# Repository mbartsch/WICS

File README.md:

WICS
====

Watering and Irrigation Control System

This is a project to integrate various devices to create a 
Control System for an irrigation system

Low Level Control:

 * USB Nano V3.0 ATmega328 16M 5V Micro-controller CH340G board For Arduino
 * Ultrasonic Sensor Module HC-SR04 Distance Measuring Sensor for arduino SR04
 * 4 Channel Relay Module With optocoupler For PIC AVR DSP ARM Arduino 8051
 * IIC I2C Logic Level Converter Bi-Directional Module 5V to 3.3V For Arduino
 * Soil Hygrometer Detection Module Soil Moisture Sensor For arduino Smart car
 * Raindrops Detection sensor modue rain module weather module Humidity For Arduino

High Level Control:
 * Raspberry Pi Model B

For the high level control, all is written in Arduino Sketch, High Level will be python/php maybe. Communication between RPi and Arduino will be over I2C (serial could be a lot easy, but I want to learn a little with this project)

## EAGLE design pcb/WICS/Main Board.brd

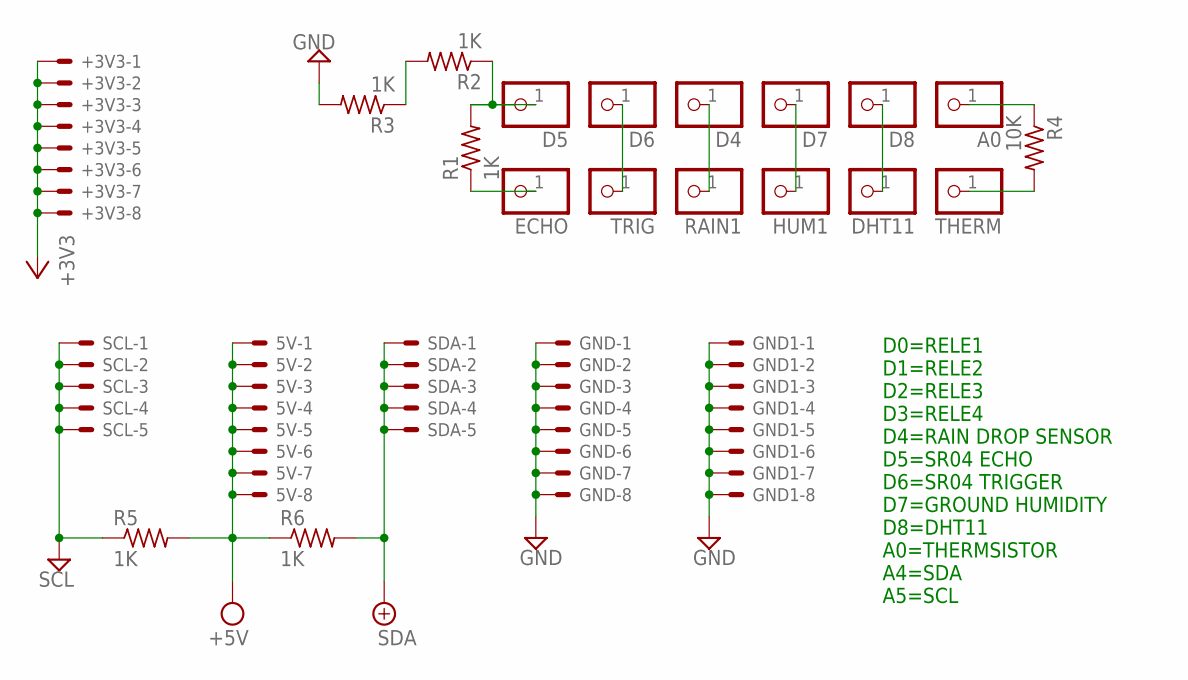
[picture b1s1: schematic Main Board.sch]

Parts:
5V: 22-23-2081
+3V3: 22-23-2081
A0: PINHD-1X1; 1X01
D4, D5, D6, D7, D8: PINHD-1X1; 1X01
DHT11: PINHD-1X1; 1X01
ECHO: PINHD-1X1; 1X01
GND, GND1: 22-23-2081
HUM1: PINHD-1X1; 1X01
R1, R2, R3, R5, R6: 1K; 0204/7
R4: 10K; 0204/7
RAIN1: PINHD-1X1; 1X01
SCL: 22-23-2051
SDA: 22-23-2051
THERM: PINHD-1X1; 1X01
TRIG: PINHD-1X1; 1X01

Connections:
+3V3: +3V3.1, +3V3.2, +3V3.3, +3V3.4, +3V3.5, +3V3.6, +3V3.7, +3V3.8
+5V: 5V.1, 5V.2, 5V.3, 5V.4, 5V.5, 5V.6, 5V.7, 5V.8, R5.2, R6.1
ECHO: ECHO.1, R1.1
GND: GND.1, GND.2, GND.3, GND.4, GND.5, GND.6, GND.7, GND.8, GND1.1, GND1.2, GND1.3, GND1.4, GND1.5, GND1.6, GND1.7, GND1.8, R3.2
GND1: R2.2, R3.1
GND3: R5.1, SCL.1, SCL.2, SCL.3, SCL.4, SCL.5
GPIO24: D5.1, R1.2, R2.1
unnamed: D6.1, TRIG.1
unnamed: A0.1, R4.1
unnamed: R4.2, THERM.1
unnamed: D4.1, RAIN1.1
unnamed: D7.1, HUM1.1
unnamed: D8.1, DHT11.1
SDA: R6.2, SDA.1, SDA.2, SDA.3, SDA.4, SDA.5

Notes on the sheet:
D0=RELE1 D1=RELE2 D2=RELE3 D3=RELE4 D4=RAIN DROP SENSOR D5=SR04 ECHO D6=SR04 TRIGGER D7=GROUND HUMIDITY D8=DHT11 A0=THERMSISTOR A4=SDA A5=SCL

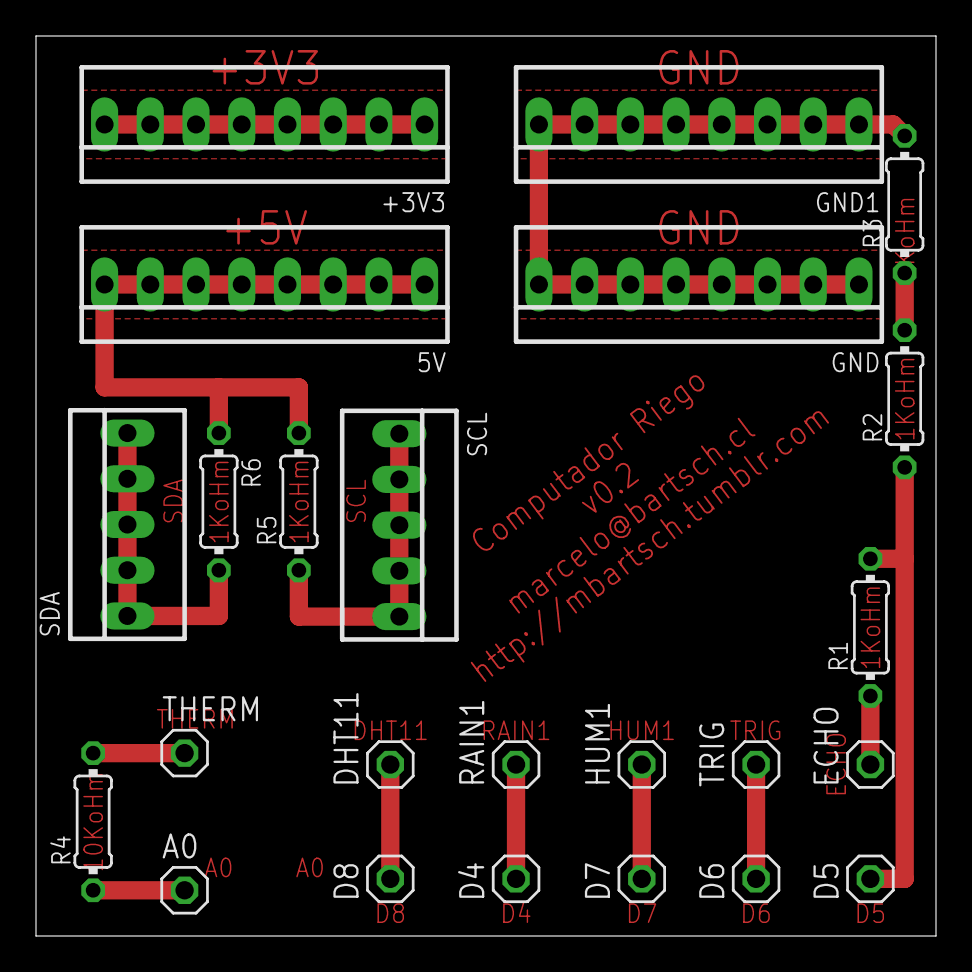
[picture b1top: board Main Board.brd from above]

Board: 2 copper layers, 50.0 x 50.0 mm, 24 parts (0 on the bottom side), 14 nets.

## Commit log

2014-10-28 WICS
2014-10-28 more ingo
2014-10-28 Moved file
2014-10-29 WICSv2 = Slave Only Version WICS = PlayGround do not use
2014-10-29 Code from Racer993 <http://raspberrypi4dummies.wordpress.com/> it will be the base for the i2c control software
2014-10-29 Changes in python code
2014-10-29 Added first status function to start testing
2014-10-29 file renamed
2014-10-30 more work, added sensor functions
2014-10-30 Added Distance Measurment
2014-10-31 Distance Sensor function
